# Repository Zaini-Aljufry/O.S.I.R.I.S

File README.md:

# O.S.I.R.I.S
Optical Sensing Intelligent Rail Inspection System
Project O.S.I.R.I.S is develop for automatic rail way inspection.
it utilize: 
  1) Windows ASP.net core framework for integration and GUI
  2) TensorFlow for object detection and classification
  3) MSSQL for database 
  4) Raspbian for Raspberry pi 4 which is place on a autonomous robot.
  
  For those interested in learning more about the project or wish to develop it further feel free to contact me.

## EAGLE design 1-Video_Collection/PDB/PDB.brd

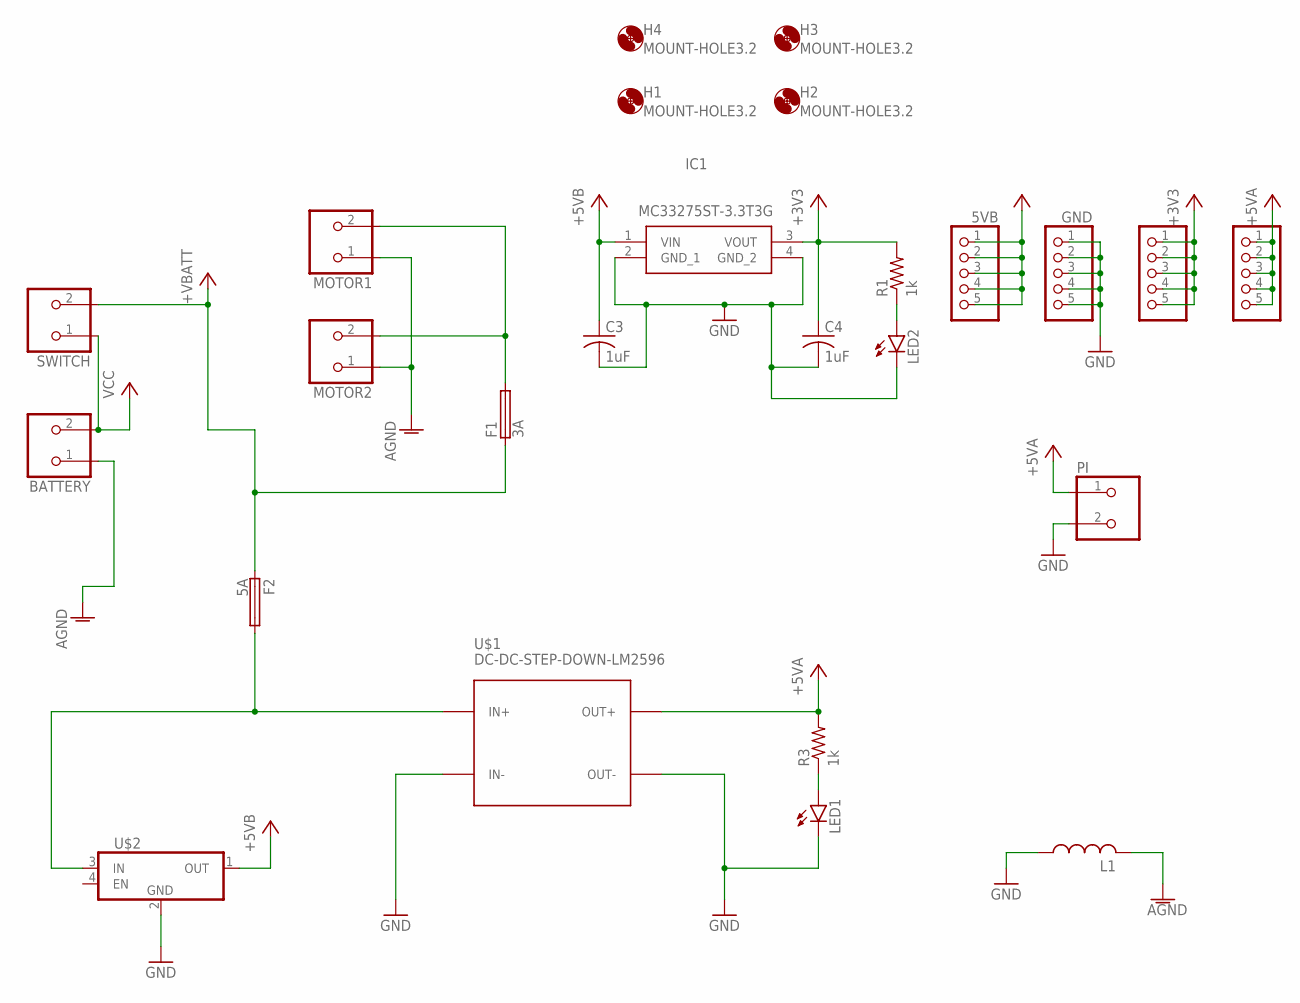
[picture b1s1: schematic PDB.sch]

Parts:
3V3, 5VA, 5VB: PINHD-1X5; 1X05
BATTERY: TERMINAL_2PINS; TERMINAL_1X2
C3, C4: 1uF; C0805
F1: 3A; SH22,5A
F2: 5A; SH22,5A
GND: PINHD-1X5; 1X05
H1, H2, H3, H4: MOUNT-HOLE3.2; 3,2
IC1: MC33275ST-3.3T3G; SOT230P700X175-4N
L1: L-USL1812; L1812
LED1, LED2: LED5MM
MOTOR1, MOTOR2: TERMINAL_2PINS; TERMINAL_1X2
PI: TERMINAL_2PINS; TERMINAL_1X2
R1, R3: 1k; R0805
SWITCH: TERMINAL_2PINS; TERMINAL_1X2
U$1: DC-DC-STEP-DOWN-LM2596
U$2: DC-DC-STEP-DOWN-MP2315

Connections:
+3V3: 3V3.1, 3V3.2, 3V3.3, 3V3.4, 3V3.5, C4.1, IC1.3 (VOUT), R1.2
+5VA: 5VA.1, 5VA.2, 5VA.3, 5VA.4, 5VA.5, PI.1, R3.2, U$1.OUT+
+5VB: 5VB.1, 5VB.2, 5VB.3, 5VB.4, 5VB.5, C3.1, IC1.1 (VIN), U$2.1 (OUT)
+VBATT: F1.1, F2.1, SWITCH.2
AGND: BATTERY.1, L1.2, MOTOR1.1, MOTOR2.1
GND: C3.2, C4.2, GND.1, GND.2, GND.3, GND.4, GND.5, IC1.2 (GND_1), IC1.4 (GND_2), L1.1, LED1.K (C), LED2.K (C), PI.2, U$1.IN-, U$1.OUT-, U$2.2 (GND)
unnamed: F1.2, MOTOR1.2, MOTOR2.2
unnamed: LED2.A, R1.1
unnamed: LED1.A, R3.1
VCC: BATTERY.2, SWITCH.1
VFUSE1: F2.2, U$1.IN+, U$2.3 (IN)

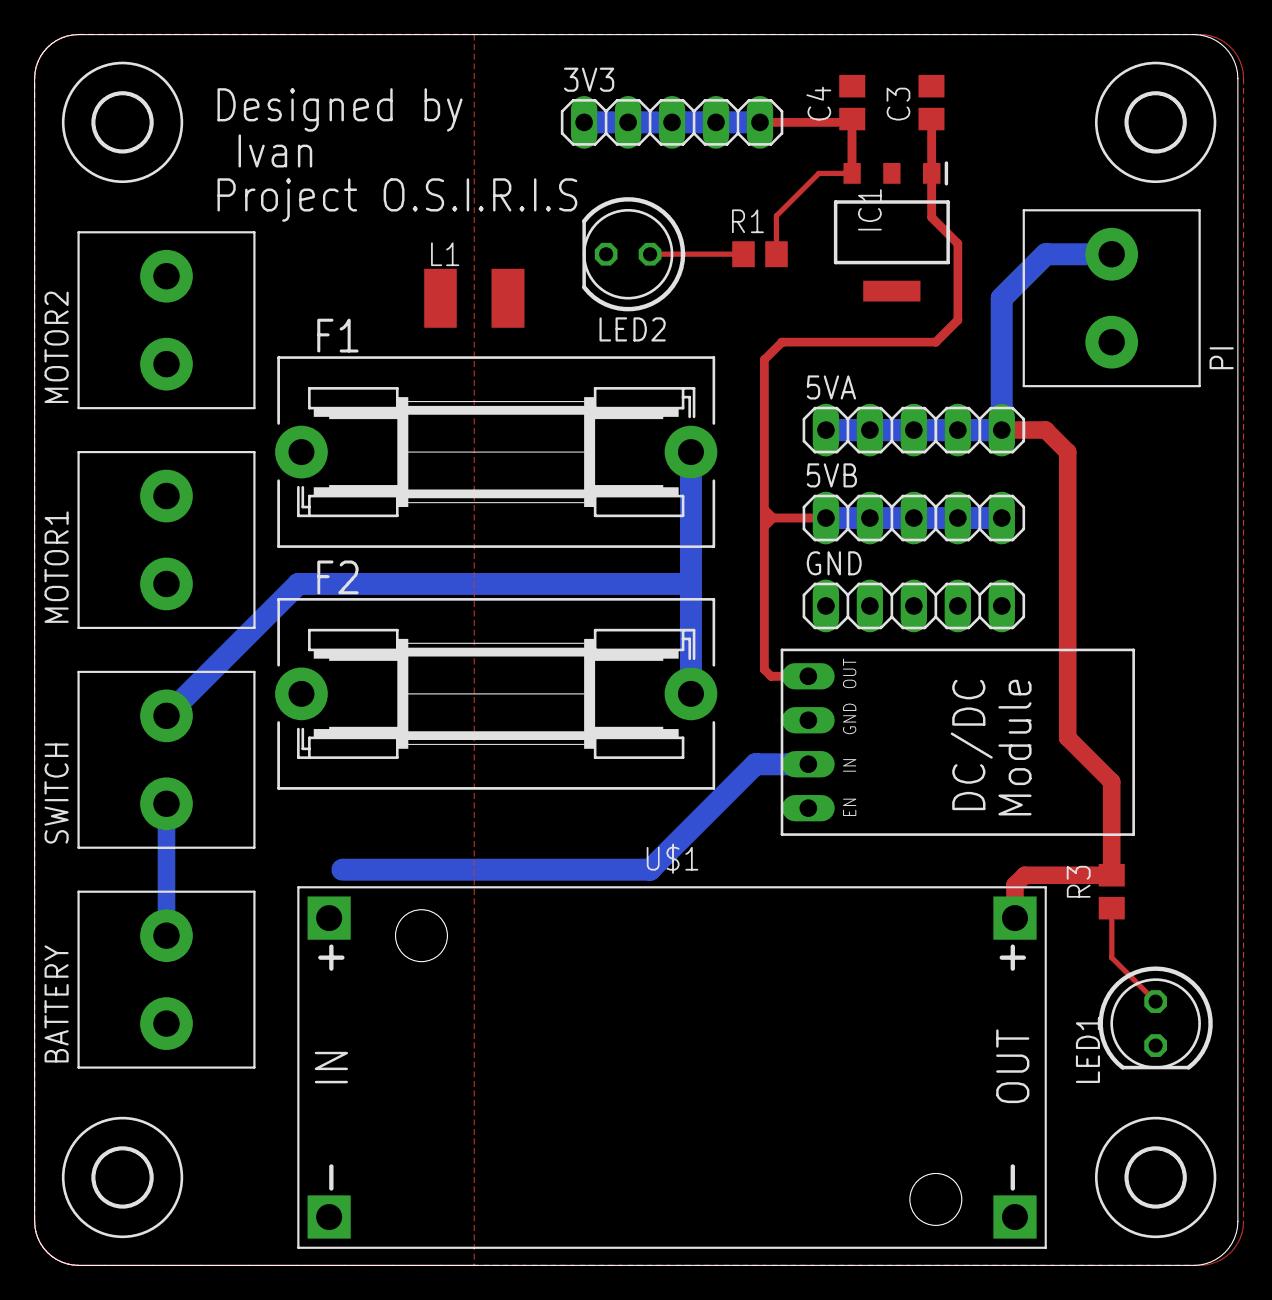
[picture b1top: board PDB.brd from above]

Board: 2 copper layers, 69.5 x 71.1 mm, 25 parts (0 on the bottom side), 11 nets.

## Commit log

2020-06-19 Project O.S.I.R.I.S

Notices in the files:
parts and their libraries:
diy-modules: Released under the Creative Commons Attribution 4.0 International License: http://creativecommons.org/licenses/by/4.0
